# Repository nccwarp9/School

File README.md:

# School,
for most students is a stressful place. School
consists mostly of tests, quizzes, and interaction with other
students and adults each with different goal in mind.
SCHOOL. uses GSR or Galvanic Skin Response
to measure the level of stress, nervousness or general
alertness of students. The GSR approach to stress detection
device have shown ability to detects whether there has
been an effort or a different situation from being relaxed
with a success rate of 90.97%. To supplement detection
temperature, accelerometer and heart rate sensor can be
added.

SCHOOL. is a arm band type device that presents
it self and functions like a smart watch to students. Device
is primarily low power bluetooth device that is set up to
automatically connect to predetermine bluetooth access
points making each classroom isolated from each other
and making device itself protected from intrusion.
Device provides information in real-time or near real
time (depending on desired resolution and battery options)
to teachers about state of attention for each student in
class and enabling them to dedicate more time for specific
student or if specific topic needs more time to be properly
adopted by students.

SCHOOL. enables students to enhance their
cognitive capabilities such as focus, ability to ignore
distractions, minimizing impuslivity. There is significant
percentage of students that are dealing with mental
health issues like ADHD, autism, dyslexia and other. This
technology can help them significantly diminish their
symptoms

This results in reducing the symptoms of ADHD,
autism, dyslexia or stress.

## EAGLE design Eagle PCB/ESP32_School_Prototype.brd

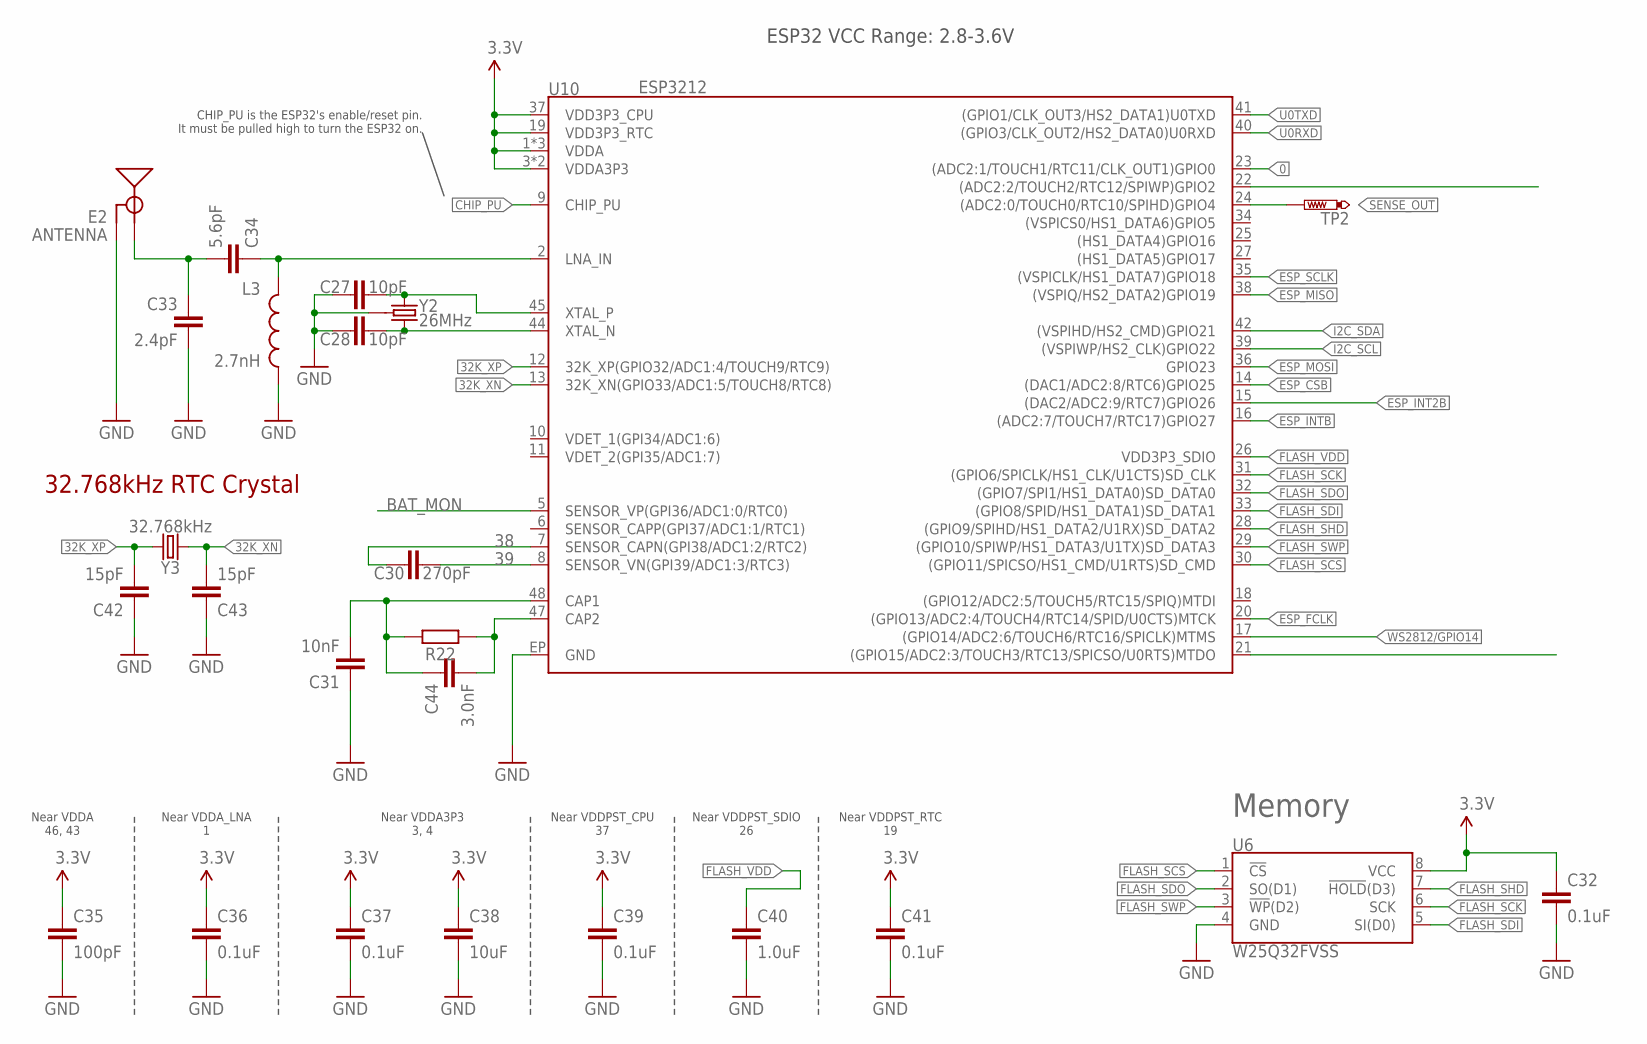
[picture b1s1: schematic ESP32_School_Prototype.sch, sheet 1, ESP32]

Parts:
C27, C28: 10pF; 0603
C30: 270pF; 0603
C31: 10nF; 0603
C32, C39: 0.1uF; 0402
C33: 2.4pF; 0603
C34: 5.6pF; 0603
C35: 100pF; 0603
C36, C37, C41: 0.1uF; 0603
C38: 10uF; 0603
C40: 1.0uF; 0603
C42, C43: 15pF; 0603
C44: 3.0nF; 0603
E2: ANTENNA; TRACE_ANTENNA_2.4GHZ_25.7MM_TUNED
L3: 2.7nH; 0603
R22: 20k; R0402
TP2: PTR1TP10SQ; TP10SQ
U6: W25Q32FVSS; SOIC-8
U10: ESP3212; QFN48-0.4MM
Y2: 26MHz; CRYSTAL-SMD-3.2X2.5
Y3: 32.768kHz; CRYSTAL-SMD-3.2X1.5MM

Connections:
0: U10.23 ((ADC2:1/TOUCH1/RTC11/CLK_OUT1)GPIO0); also elsewhere on the board
3.3V: C32.1, C35.1, C36.1, C37.1, C38.1, C39.1, C41.1, U6.8 (VCC), U10.1 (VDDA), U10.3 (VDDA3P3), U10.4 (VDDA3P3), U10.19 (VDD3P3_RTC), U10.37 (VDD3P3_CPU), U10.43 (VDDA), U10.46 (VDDA); also elsewhere on the board
32K_XN: C43.2, U10.13 (32K_XN(GPIO33/ADC1:5/TOUCH8/RTC8)), Y3.P$2 (2)
32K_XP: C42.2, U10.12 (32K_XP(GPIO32/ADC1:4/TOUCH9/RTC9)), Y3.P$1 (1)
38: C30.1, U10.7 (SENSOR_CAPN(GPI38/ADC1:2/RTC2))
39: C30.2, U10.8 (SENSOR_VN(GPI39/ADC1:3/RTC3))
BAT_MON: U10.5 (SENSOR_VP(GPI36/ADC1:0/RTC0)); also elsewhere on the board
CAP_10N: C31.2, C44.1, R22.2, U10.48 (CAP1)
CHIP_PU: U10.9 (CHIP_PU); also elsewhere on the board
ESP_CSB: U10.14 ((DAC1/ADC2:8/RTC6)GPIO25)
ESP_FCLK: U10.20 ((GPIO13/ADC2:4/TOUCH4/RTC14/SPID/U0CTS)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)
ESP_INT2B: U10.15 ((DAC2/ADC2:9/RTC7)GPIO26)
ESP_INTB: U10.16 ((ADC2:7/TOUCH7/RTC17)GPIO27)
ESP_MISO: U10.38 ((VSPIQ/HS2_DATA2)GPIO19)
ESP_MOSI: U10.36 (GPIO23)
ESP_SCLK: U10.35 ((VSPICLK/HS1_DATA7)GPIO18)
FLASH_SCK: U6.6 (SCK), U10.31 ((GPIO6/SPICLK/HS1_CLK/U1CTS)SD_CLK)
FLASH_SCS: U6.1 (!CS!), U10.30 ((GPIO11/SPICSO/HS1_CMD/U1RTS)SD_CMD)
FLASH_SDI: U6.5 (SI(D0)), U10.33 ((GPIO8/SPID/HS1_DATA1)SD_DATA1)
FLASH_SDO: U6.2 (SO(D1)), U10.32 ((GPIO7/SPI1/HS1_DATA0)SD_DATA0)
FLASH_SHD: U6.7 (!HOLD!(D3)), U10.28 ((GPIO9/SPIHD/HS1_DATA2/U1RX)SD_DATA2)
FLASH_SWP: U6.3 (!WP!(D2)), U10.29 ((GPIO10/SPIWP/HS1_DATA3/U1TX)SD_DATA3)
FLASH_VDD: C40.1, U10.26 (VDD3P3_SDIO)
GND: C27.1, C28.1, C31.1, C32.2, C33.2, C35.2, C36.2, C37.2, C38.2, C39.2, C40.2, C41.2, C42.1, C43.1, E2.GND, E2.GND2 (GND), L3.2, U6.4 (GND), U10.EP (GND), Y2.2 (GND), Y2.4 (GND); also elsewhere on the board
I2C_SCL: U10.39 ((VSPIWP/HS2_CLK)GPIO22); also elsewhere on the board
I2C_SDA: U10.42 ((VSPIHD/HS2_CMD)GPIO21); also elsewhere on the board
LNA_IN: C34.1, L3.1, U10.2 (LNA_IN)
unnamed: C27.2, U10.45 (XTAL_P), Y2.1
unnamed: C28.2, U10.44 (XTAL_N), Y2.3 (2)
unnamed: C44.2, R22.1, U10.47 (CAP2)
SENSE_OUT: TP2.TP, U10.24 ((ADC2:0/TOUCH0/RTC10/SPIHD)GPIO4); also elsewhere on the board
TRACE_ANT1: C33.1, C34.2, E2.ANT (SIGNAL)
U0RXD: U10.40 ((GPIO3/CLK_OUT2/HS2_DATA0)U0RXD); also elsewhere on the board
U0TXD: U10.41 ((GPIO1/CLK_OUT3/HS2_DATA1)U0TXD); also elsewhere on the board
WS2812/GPIO14: U10.17 ((GPIO14/ADC2:6/TOUCH6/RTC16/SPICLK)MTMS); also elsewhere on the board

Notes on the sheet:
Near VDDA 46, 43
Near VDDA_LNA 1
Near VDDA3P3 3, 4
Near VDDPST_CPU 37
Near VDDPST_SDIO 26
Near VDDPST_RTC 19
32.768kHz RTC Crystal
ESP32 VCC Range: 2.8-3.6V
CHIP_PU is the ESP32's enable/reset pin. It must be pulled high to turn the ESP32 on.
Memory

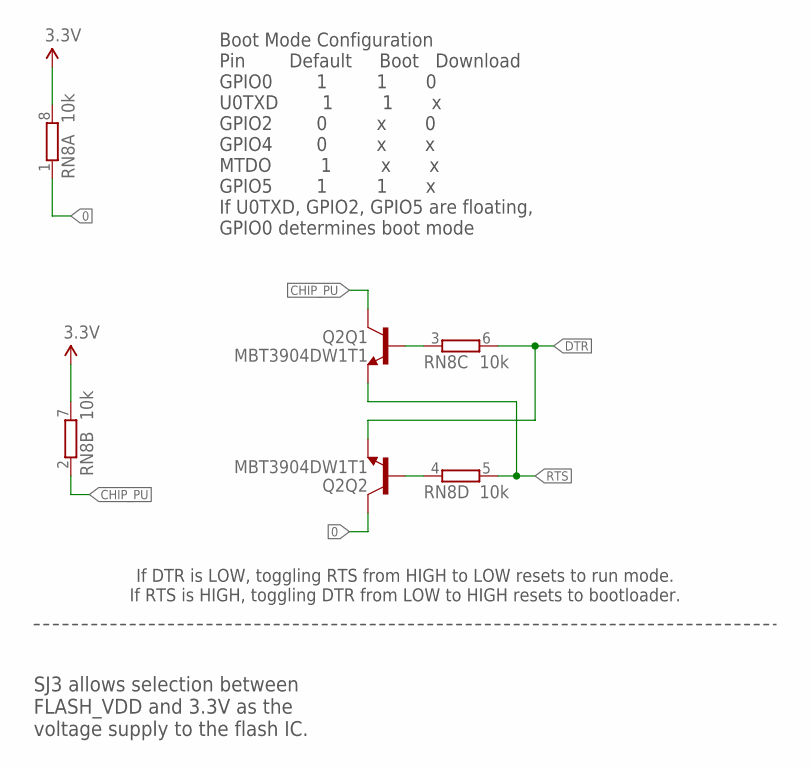
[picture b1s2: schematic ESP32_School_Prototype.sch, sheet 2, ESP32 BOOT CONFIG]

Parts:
Q2: MBT3904DW1T1; SC70-6
RN8: 10k; 0603-ARC

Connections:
0: Q2.6 (C), RN8.1; also elsewhere on the board
3.3V: RN8.7 (2), RN8.8 (2); also elsewhere on the board
CHIP_PU: Q2.3 (C), RN8.2 (1); also elsewhere on the board
DTR: Q2.1 (E), RN8.6 (2); also elsewhere on the board
unnamed: Q2.5 (B), RN8.3 (1)
unnamed: Q2.2 (B), RN8.4 (1)
RTS: Q2.4 (E), RN8.5 (2); also elsewhere on the board

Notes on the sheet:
Boot Mode Configuration Pin Default Boot Download GPIO0 1 1 0 U0TXD 1 1 x GPIO2 0 x 0 GPIO4 0 x x MTDO 1 x x GPIO5 1 1 x If U0TXD, GPIO2, GPIO5 are floating, GPIO0 determines boot mode
SJ3 allows selection between FLASH_VDD and 3.3V as the voltage supply to the flash IC.
If DTR is LOW, toggling RTS from HIGH to LOW resets to run mode. If RTS is HIGH, toggling DTR from LOW to HIGH resets to bootloader.

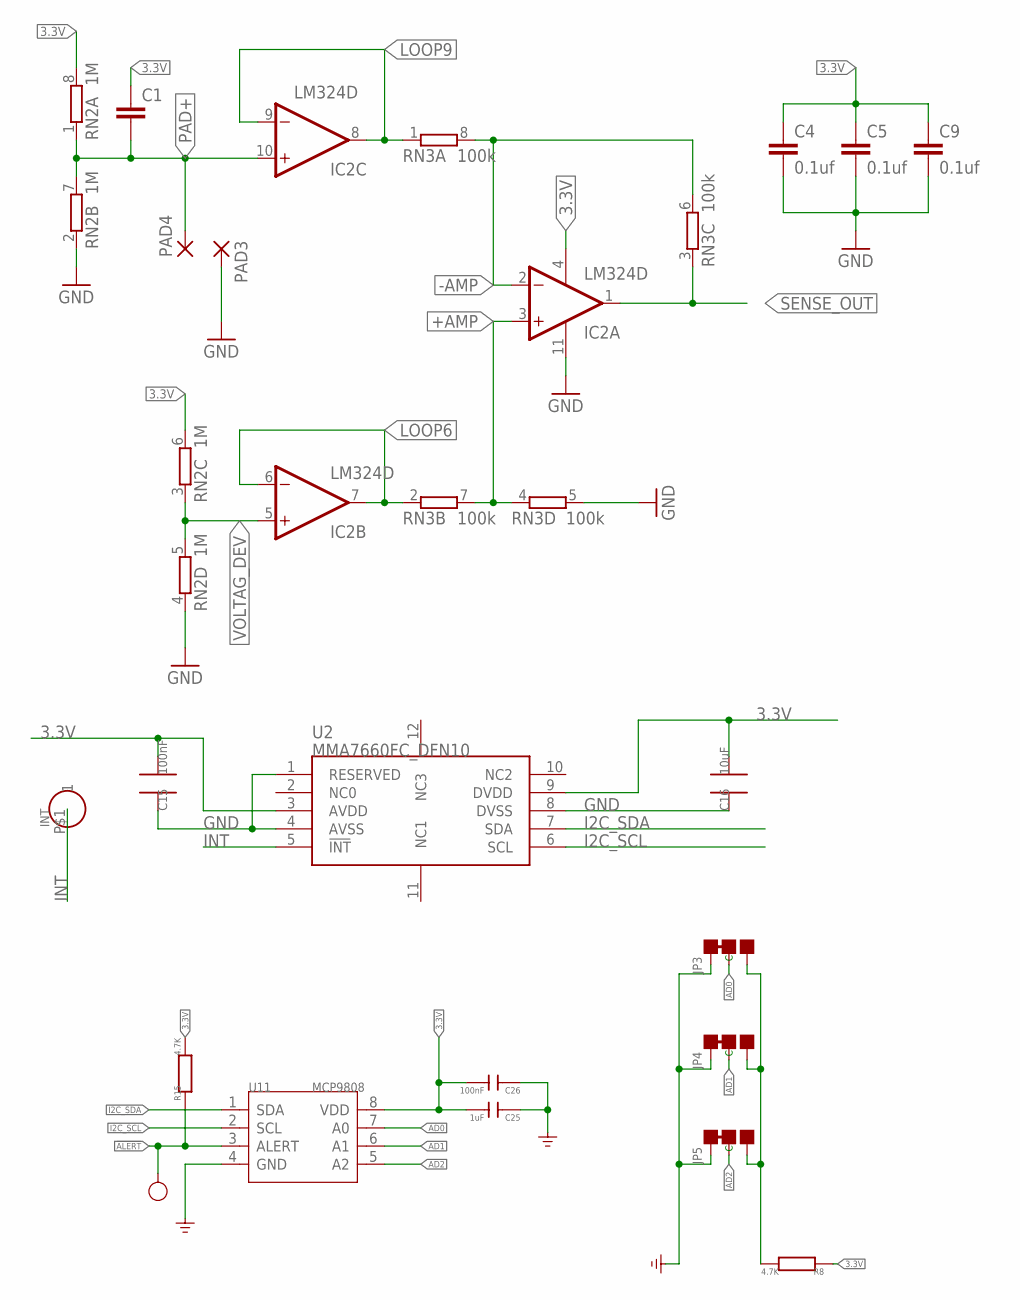
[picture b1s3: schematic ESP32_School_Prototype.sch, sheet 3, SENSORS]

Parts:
C1: C-EUC0603K; C0603K
C4, C5, C9: 0.1uf; C0603K
C15: 100nF; 0603_S
C16: 10uF; 0805_S
C25: 1uF; C0603
C26: 100nF; C0603
GND16: TEST-POINT'4545'; TP-D45MIL
IC2: LM324D; SO14
INT: HEADER-1P-35; 1P-65/35MIL
JP3, JP4, JP5: JP-3P-SHORT; 3P-SMD-SHORT
PAD3, PAD4: 2,54/1,1
R8, R15: 4.7K; R0402
RN2: 1M; 0603-ARV
RN3: 100k; 0603-ARV
U2: MMA7660FC_DFN10; DFN10
U11: MCP9808; MSOP8-0.65-3X3X0.85MM

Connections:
3.3V: C1.1, C4.1, C5.1, C9.1, C15.2, C16.2, C25.2, C26.2, IC2.4 (V+), R8.1, R15.2, RN2.6 (2), RN2.8 (2), U2.3 (AVDD), U2.9 (DVDD), U11.8 (VDD); also elsewhere on the board
!ALERT: GND16.T, R15.1, U11.3 (ALERT)
+AMP: IC2.3 (+IN), RN3.4 (1), RN3.7 (2)
-AMP: IC2.2 (-IN), RN3.6 (2), RN3.8 (2)
AD0: JP3.MM (C), U11.7 (A0)
AD1: JP4.MM (C), U11.6 (A1)
AD2: JP5.MM (C), U11.5 (A2)
GND: C4.2, C5.2, C9.2, C15.1, C16.1, C25.1, C26.1, IC2.11 (V-), JP3.11 (L), JP4.11 (L), JP5.11 (L), PAD3.1, RN2.2 (1), RN2.4 (1), RN3.5 (2), U2.1 (RESERVED), U2.4 (AVSS), U2.8 (DVSS), U11.4 (GND); also elsewhere on the board
I2C_SCL: U2.6 (SCL), U11.2 (SCL); also elsewhere on the board
I2C_SDA: U2.7 (SDA), U11.1 (SDA); also elsewhere on the board
INT: INT.P$1, U2.5 (!INT)
LOOP6: IC2.6 (-IN), IC2.7 (OUT), RN3.2 (1)
LOOP9: IC2.8 (OUT), IC2.9 (-IN), RN3.1
unnamed: JP3.00 (R), JP4.00 (R), JP5.00 (R), R8.2
PAD+: C1.2, IC2.10 (+IN), PAD4.1, RN2.1, RN2.7 (2)
SENSE_OUT: IC2.1 (OUT), RN3.3 (1); also elsewhere on the board
VOLTAG_DEV: IC2.5 (+IN), RN2.3 (1), RN2.5 (2)

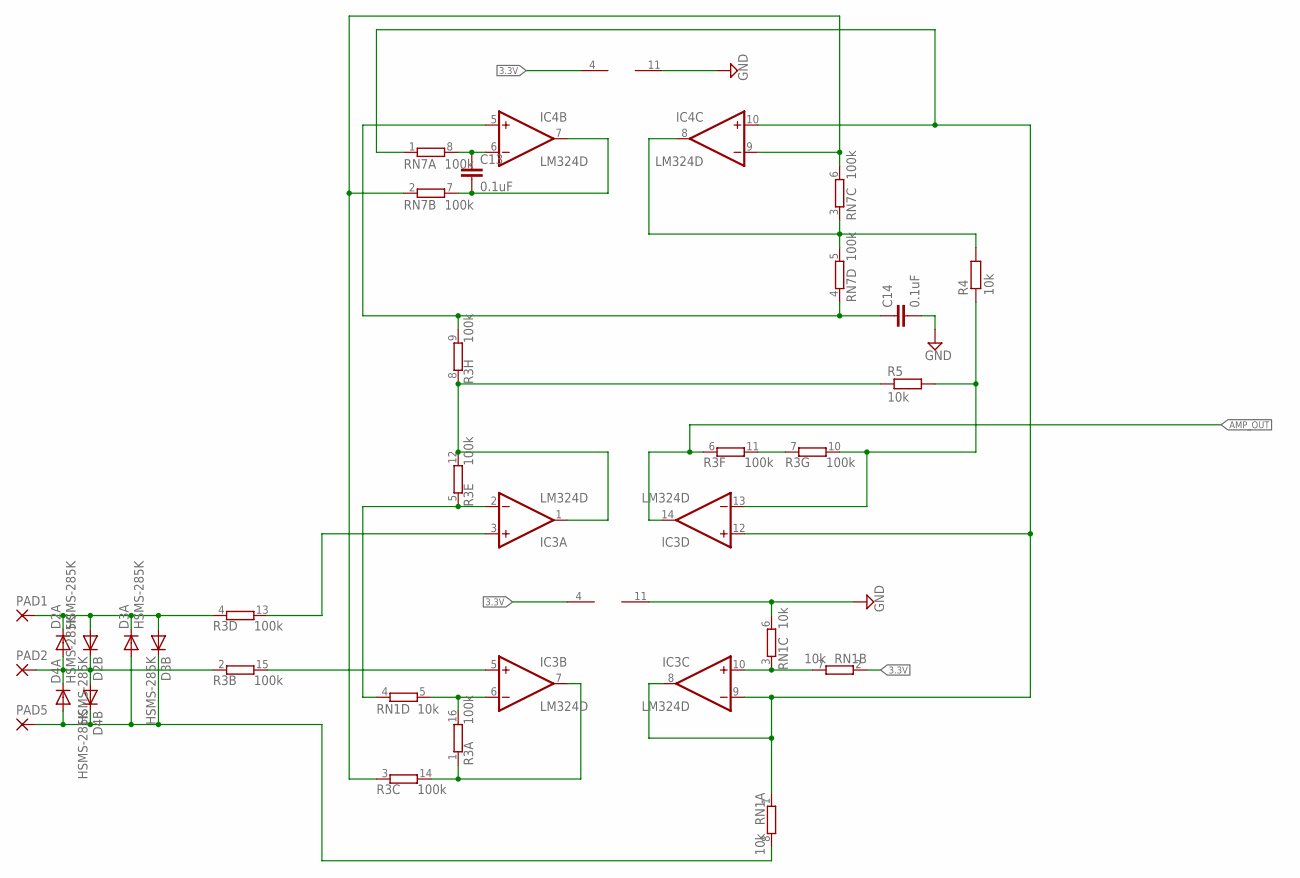
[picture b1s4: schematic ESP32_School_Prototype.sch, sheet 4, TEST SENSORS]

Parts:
C13, C14: 0.1uF; 0402
D2, D3, D4: HSMS-285K; SOT363
IC3, IC4: LM324D; SO14
PAD1, PAD2, PAD5: 2,54/1,1
R3: 100k; EXB2HV
R4, R5: 10k; R0603
RN1: 10k; 4X0402ARV341
RN7: 100k; 4X0402ARV341

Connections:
3.3V: IC3.4 (V+), IC4.4 (V+), RN1.2 (1); also elsewhere on the board
AMP_OUT: IC3.14 (OUT), R3.6 (1)
GND: C14.2, IC3.11 (V-), IC4.11 (V-), RN1.6 (2); also elsewhere on the board
unnamed: D2.3 (A), D2.6 (C), D3.3 (A), D3.6 (C), PAD1.1, R3.4 (1)
unnamed: D2.1 (A), D2.4 (C), D4.3 (A), D4.6 (C), PAD2.1, R3.2 (1)
unnamed: D3.1 (A), D3.4 (C), D4.1 (A), D4.4 (C), PAD5.1, RN1.8 (2)
unnamed: IC3.10 (+IN), RN1.3 (1), RN1.7 (2)
unnamed: IC3.7 (OUT), R3.1, R3.14 (2)
unnamed: IC3.6 (-IN), R3.16 (2), RN1.5 (2)
unnamed: IC4.9 (-IN), R3.3 (1), RN7.2 (1), RN7.6 (2)
unnamed: IC3.2 (-IN), R3.5 (1), RN1.4 (1)
unnamed: IC3.5 (+IN), R3.15 (2)
unnamed: IC3.3 (+IN), R3.13 (2)
unnamed: IC3.1 (OUT), R3.8 (1), R3.12 (2), R5.1
unnamed: IC3.13 (-IN), R3.10 (2), R4.1, R5.2
unnamed: IC4.8 (OUT), R4.2, RN7.3 (1), RN7.5 (2)
unnamed: R3.7 (1), R3.11 (2)
unnamed: C14.1, IC4.5 (+IN), R3.9 (2), RN7.4 (1)
unnamed: C13.1, IC4.6 (-IN), RN7.8 (2)
unnamed: IC3.8 (OUT), IC3.9 (-IN), IC3.12 (+IN), IC4.10 (+IN), RN1.1, RN7.1
unnamed: C13.2, IC4.7 (OUT), RN7.7 (2)

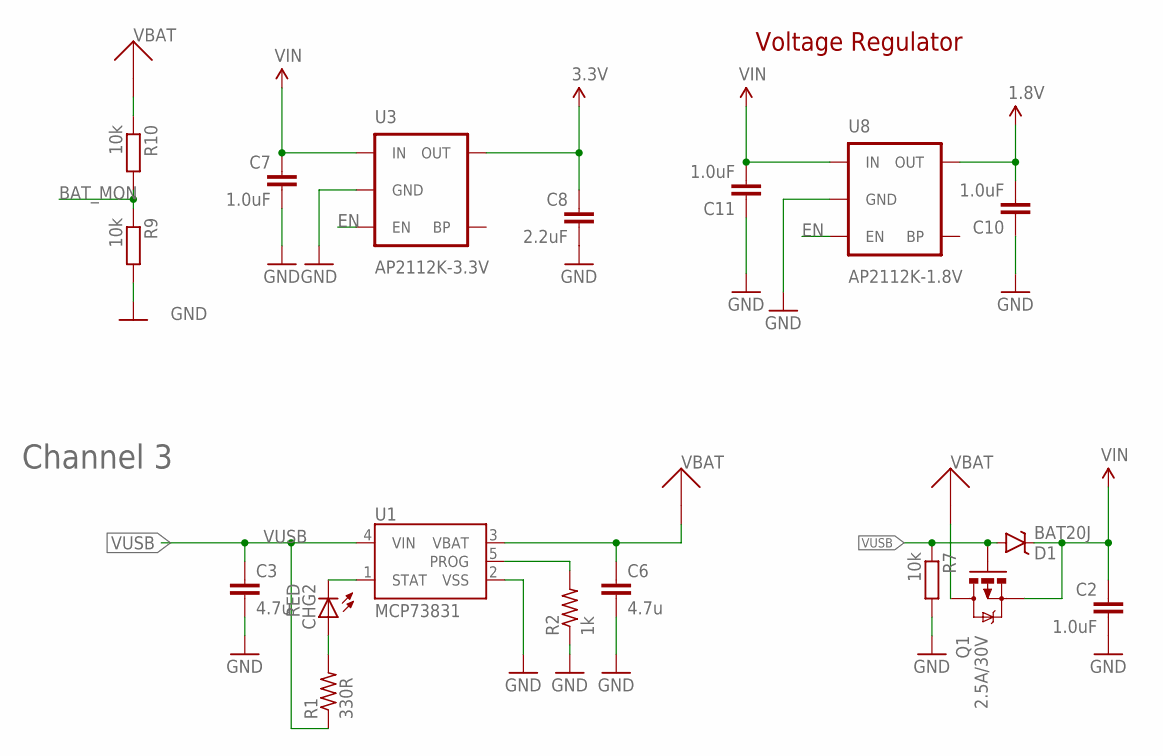
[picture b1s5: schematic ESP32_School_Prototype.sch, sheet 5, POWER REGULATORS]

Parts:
C2: 1.0uF; C0402
C3, C6: 4.7u; C0805
C7: 1.0uF; 0805
C8: 2.2uF; C0805
C10, C11: 1.0uF; C0805
CHG2: RED; CHIPLED_0603
D1: BAT20J; SOD-323
Q1: 2.5A/30V; SOT23-3
R1: 330R; R0402
R2: 1k; R0402
R7, R9, R10: 10k; R0402
U1: MCP73831; SOT23-5
U3: AP2112K-3.3V; SOT23-5
U8: AP2112K-1.8V; SOT23-5

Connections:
1.8V: C10.2, U8.5 (OUT)
3.3V: C8.1, U3.5 (OUT); also elsewhere on the board
BAT_MON: R9.1, R10.2; also elsewhere on the board
EN: U3.3 (EN), U8.3 (EN); also elsewhere on the board
GND: C2.2, C3.2, C6.2, C7.2, C8.2, C10.1, C11.1, R2.1, R7.2, R9.2, U1.2 (VSS), U3.2 (GND), U8.2 (GND); also elsewhere on the board
unnamed: CHG2.C, U1.1 (STAT)
unnamed: CHG2.A, R1.2
unnamed: R2.2, U1.5 (PROG)
VBAT: C6.1, Q1.3 (D), R10.1, U1.3 (VBAT); also elsewhere on the board
VIN: C2.1, C7.1, C11.2, D1.C, Q1.2 (S), U3.1 (IN), U8.1 (IN); also elsewhere on the board
VUSB: C3.1, D1.A, Q1.1 (G), R1.1, R7.1, U1.4 (VIN); also elsewhere on the board

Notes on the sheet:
Channel 3
Voltage Regulator

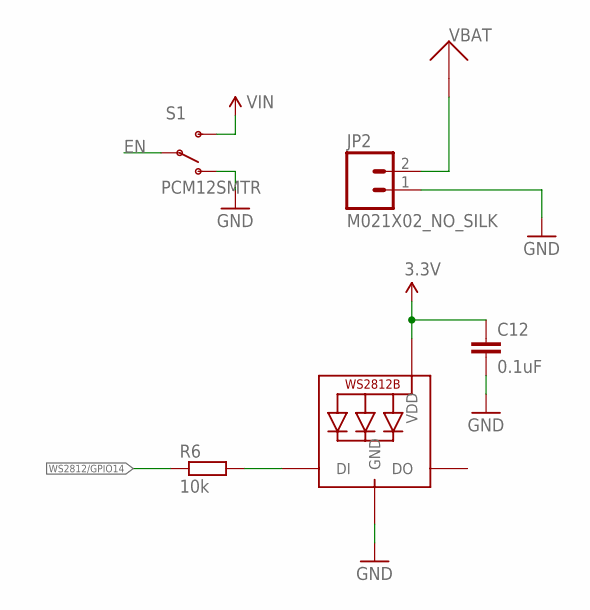
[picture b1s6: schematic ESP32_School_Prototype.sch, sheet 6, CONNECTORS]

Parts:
C12: 0.1uF; 0603
JP2: M021X02_NO_SILK; 1X02_NO_SILK
LED2: WS2812B5050; WS2812B
R6: 10k; R0402
S1: PCM12SMTR; SWITCH-SPST-SMD-A

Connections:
3.3V: C12.1, LED2.1-VDD (VDD); also elsewhere on the board
EN: S1.2; also elsewhere on the board
GND: C12.2, JP2.1, LED2.3-GND (GND), S1.1 (O); also elsewhere on the board
unnamed: LED2.4-DIN (DI), R6.2
VBAT: JP2.2; also elsewhere on the board
VIN: S1.3 (S); also elsewhere on the board
WS2812/GPIO14: R6.1; also elsewhere on the board

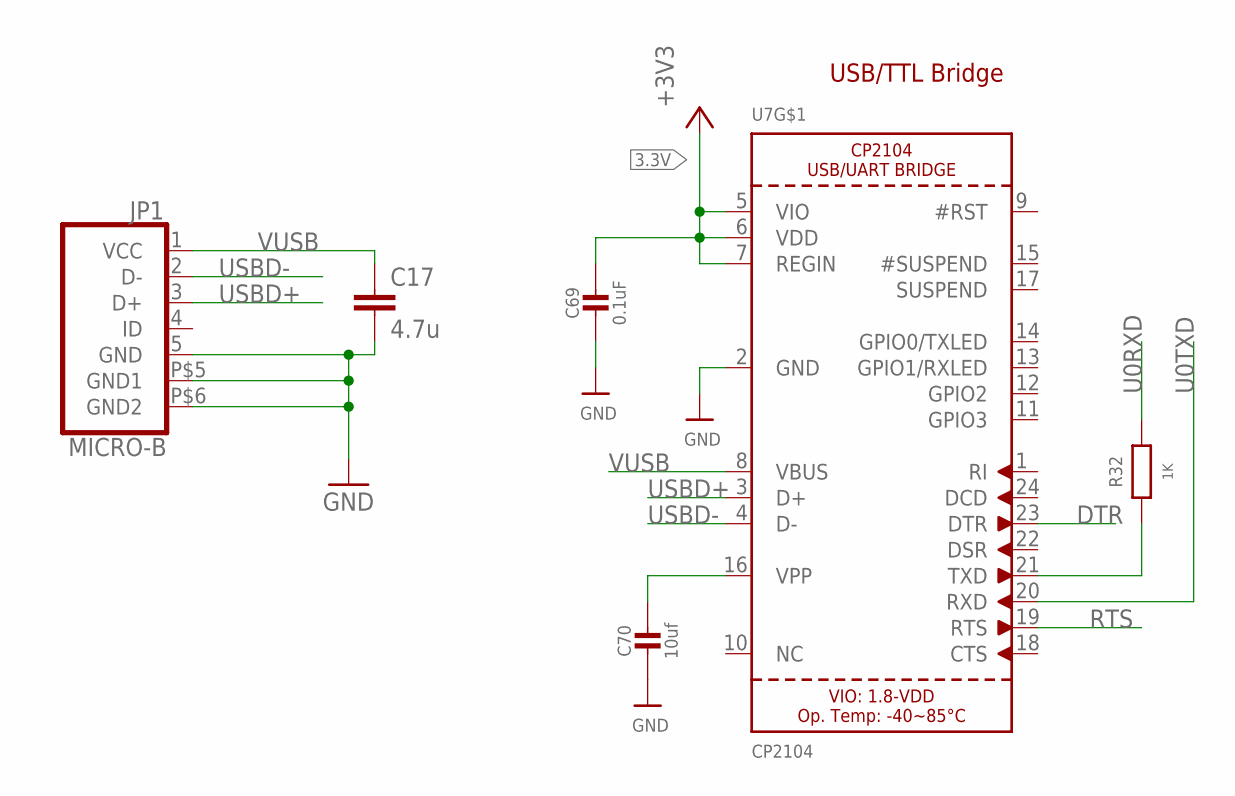
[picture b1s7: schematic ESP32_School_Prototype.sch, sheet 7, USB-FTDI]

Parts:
C17: 4.7u; C0805
C69: 0.1uF; _0402
C70: 10uf; 0805-NO
JP1: MICRO-B
R32: 1K; R0402
U7: CP2104; QFN24_4MM_SMSC

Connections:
3.3V: C69.1, U7.5 (VIO), U7.6 (VDD), U7.7 (REGIN); also elsewhere on the board
DTR: U7.23 (DTR); also elsewhere on the board
GND: C17.2, C69.2, C70.2, JP1.5 (GND), JP1.P$5 (GND1), JP1.P$6 (GND2), U7.2 (GND); also elsewhere on the board
unnamed: R32.1, U7.21 (TXD)
unnamed: C70.1, U7.16 (VPP)
RTS: U7.19 (RTS); also elsewhere on the board
TP: U7.THERM (TP)
U0RXD: R32.2; also elsewhere on the board
U0TXD: U7.20 (RXD); also elsewhere on the board
USBD+: JP1.3 (D+), U7.3 (D+)
USBD-: JP1.2 (D-), U7.4 (D-)
VUSB: C17.1, JP1.1 (VCC), U7.8 (VBUS); also elsewhere on the board

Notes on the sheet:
USB/TTL Bridge

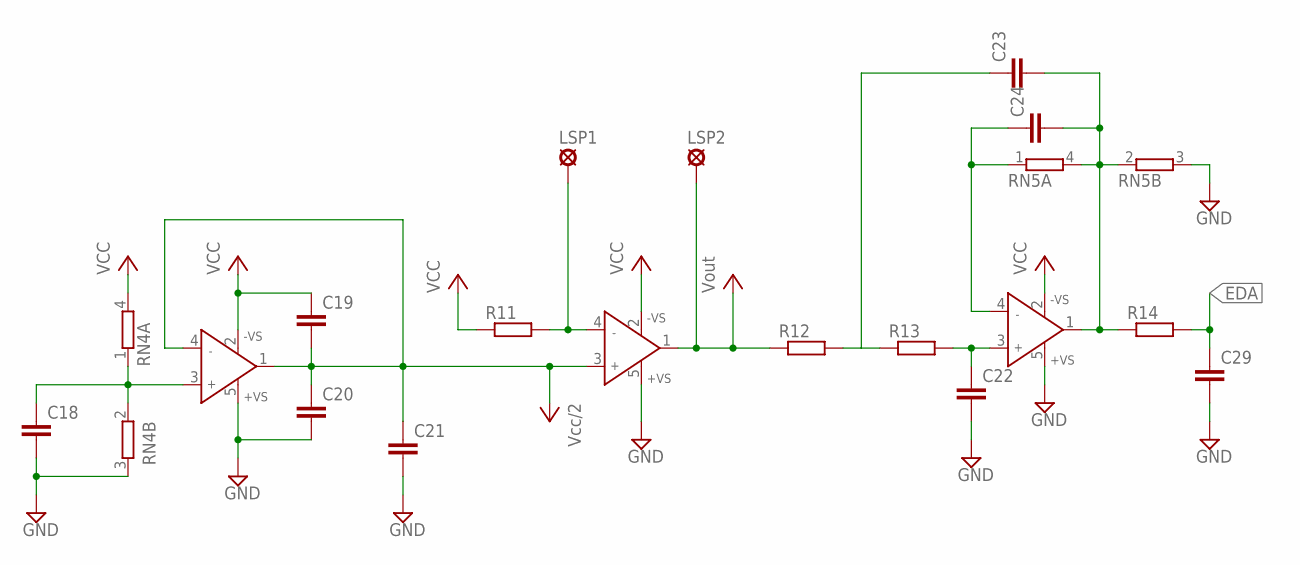
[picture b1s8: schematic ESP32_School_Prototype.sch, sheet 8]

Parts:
C18, C19, C20, C21, C22, C23, C24, C29: C-EUC0201; C0201
IC1, IC5, IC6: AD8603UJ; SOT23-5
LSP1, LSP2: MCS08
R11, R12, R13, R14: R-EU_M2012; M2012
RN4, RN5: 2R-NEXBV4V; EXBV4V

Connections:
EDA: C29.1, R14.2
GND: C18.2, C20.2, C21.2, C22.2, C29.2, IC1.5 (+VS), IC5.5 (+VS), IC6.5 (+VS), RN4.3 (2), RN5.3 (2); also elsewhere on the board
unnamed: IC5.4 (IN-), LSP1.MP, R11.2
unnamed: C18.1, IC1.3 (IN+), RN4.1, RN4.2 (1)
unnamed: C23.1, R12.2, R13.1
unnamed: C22.1, IC6.3 (IN+), R13.2
unnamed: C24.1, IC6.4 (IN-), RN5.1
unnamed: C23.2, C24.2, IC6.1 (OUT), R14.1, RN5.2 (1), RN5.4 (2)
VCC: C19.1, C19.2, C20.1, C21.1, IC1.1 (OUT), IC1.2 (-VS), IC1.4 (IN-), IC5.1 (OUT), IC5.2 (-VS), IC5.3 (IN+), IC6.2 (-VS), LSP2.MP, R11.1, R12.1, RN4.4 (2)

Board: 2 copper layers, 112 parts (0 on the bottom side), 84 nets, no tracks yet.

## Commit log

2019-09-30 First Full Commit
2019-09-30 PCB Added
2019-09-30 PCB file
2019-09-30 Folder Name Change

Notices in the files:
parts and their libraries:
SparkFun-Capacitors: Licensing: Creative Commons ShareAlike 4.0 International - https://creativecommons.org/licenses/by-sa/4.0
microbuilder: This work is placed in the public domain, and may be freely used for commercial and non-commercial work with the following conditions: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
